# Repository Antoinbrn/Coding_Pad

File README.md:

# Taz Pad
Taz pad is a 4 key macropad, has 2 LED and works with kmk firmware.

## Firmware:
- An EC11 Rotary encoder to change volume and to mute.
- A switch to open gmail.
- A switch to open calculator.
- 2 WS2812B RGB LEDs. Both diffusing across the display.
- 4 Cherry MX-style keys.

## CAD:
The case is composed of 2 different parts. The Top and the Bottom
The case fits together with 3 M6 screws.

Top CAD

Bottom CAD

## PCB:
Here is my pcb made in KiCad

## Firmware:
This macro pad uses KMK
- the rotary encoder changes the volume, press to mute.
- Copy, Paste, Gmail, and calculator button.

## BOM:
- 4x Cherry MX Switches
- 4x DSA Keycaps
- 3x M3x16mm screws
- 5x 1N4148 DO-35 Diodes.
- 2x WS2812B LEDs
- 1x EC11 Rotary Encoder
- 1x XIAO RP2040
- 1x Case (2 printed parts)

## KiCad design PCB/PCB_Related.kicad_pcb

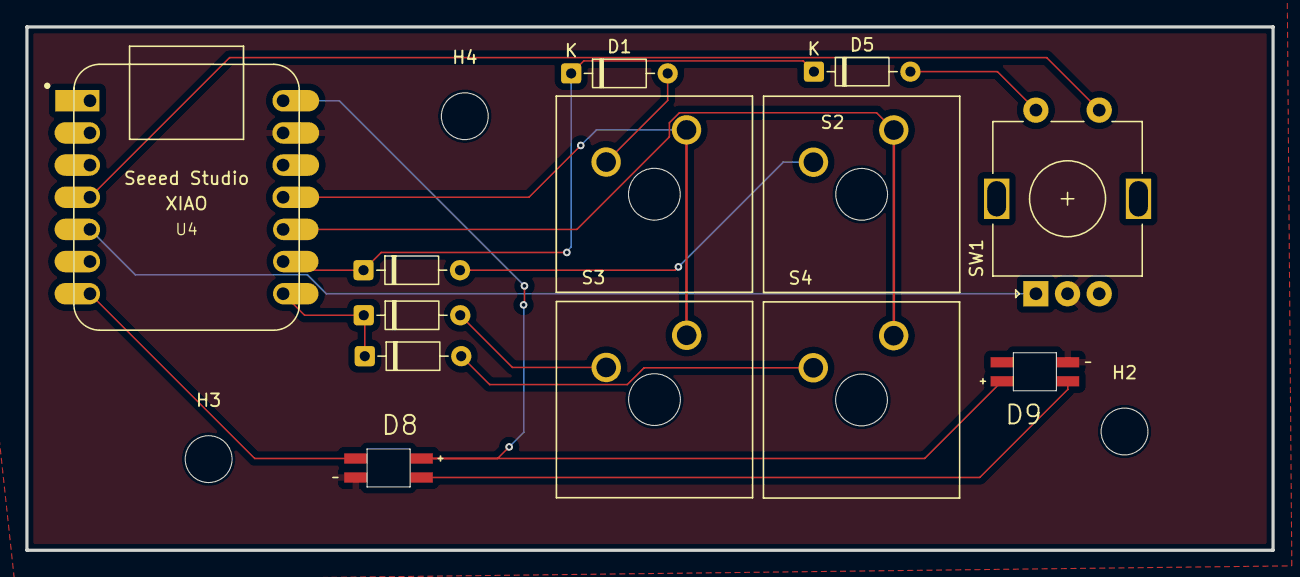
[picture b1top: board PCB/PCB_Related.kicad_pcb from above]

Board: 4 copper layers, 98.4 x 41.3 mm, 16 parts (0 on the bottom side), 16 nets.

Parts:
D1, D2, D3, D4, D5: D_Small; D_DO-35_SOD27_P7.62mm_Horizontal
D8, D9: SK6812-E; LED_SK6812-E
H2, H3, H4: MountingHole; MountingHole_3.7mm
S1, S2, S3, S4: MX1A-11NN; SW_MX1A-11NN
SW1: RotaryEncoder_Switch; RotaryEncoder_Alps_EC11E-Switch_Vertical_H20mm
U4: MOUDLE-SEEEDUINO-XIAO; XIAO-Generic-Hybrid-14P-2.54-21X17.8MM

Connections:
A: D5.2 (A), SW1.S2
AUP: SW1.A, U4.5 (PA8_A4_D4_SDA)
B: SW1.S1, U4.4 (PA11_A3_D3)
BDOWN: SW1.B, U4.6 (PA9_A5_D5_SCL)
COL0: S1.2, S3.2, U4.11 (PA6_A10_D10_MOSI)
COL1: S2.2, S4.2, U4.10 (PA5_A9_D9_MISO)
GND: D8.3 (GND), D9.3 (GND), SW1.C, U4.13 (GND)
LED: D8.4 (DIN), U4.7 (PB08_A6_D6_TX)
unnamed: D1.2 (A), S1.1
unnamed: D2.2 (A), S2.1
unnamed: D3.2 (A), S3.1
unnamed: D4.2 (A), S4.1
unnamed: D8.2 (DOUT), D9.4 (DIN)
ROW0: D1.1 (K), D2.1 (K), D5.1 (K), U4.9 (PA7_A8_D8_SCK)
ROW1: D3.1 (K), D4.1 (K), U4.8 (PB09_A7_D7_RX)
VCC: D8.1 (VDD), D9.1 (VDD), U4.14 (5V)

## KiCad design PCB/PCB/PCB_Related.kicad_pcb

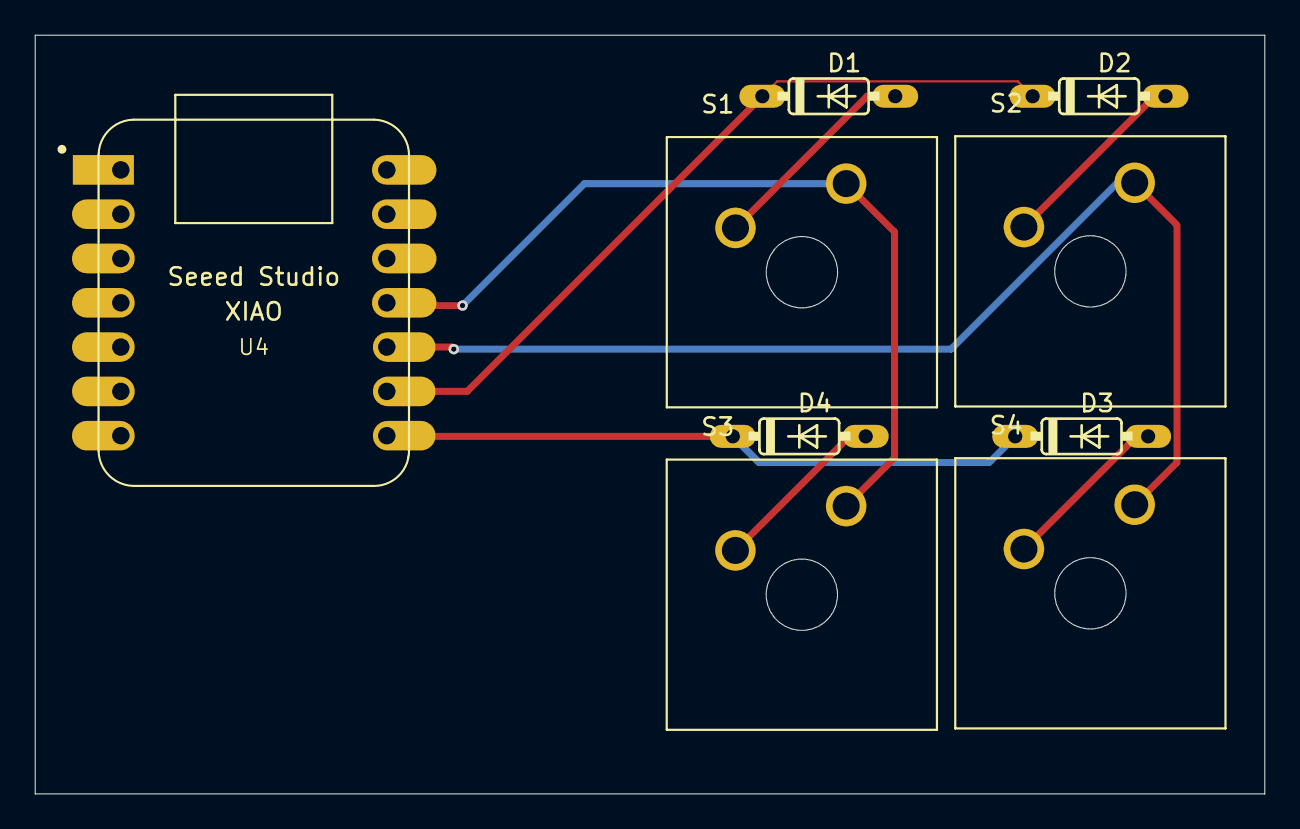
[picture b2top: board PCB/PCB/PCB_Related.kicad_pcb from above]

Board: 4 copper layers, 70.5 x 43.5 mm, 9 parts (0 on the bottom side), 8 nets.

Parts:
D1, D2, D3, D4: 1N4148; DO35-7
S1, S2, S3, S4: MX1A-11NN; SW_MX1A-11NN
U4: MOUDLE-SEEEDUINO-XIAO; XIAO-Generic-Hybrid-14P-2.54-21X17.8MM

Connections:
COL0: S1.2, S3.2, U4.11 (PA6_A10_D10_MOSI)
COL1: S2.2, S4.2, U4.10 (PA5_A9_D9_MISO)
unnamed: D1.A, S1.1
unnamed: D2.A, S2.1
unnamed: D3.A, S4.1
unnamed: D4.A, S3.1
ROW0: D1.C, D2.C, U4.9 (PA7_A8_D8_SCK)
ROW1: D3.C, D4.C, U4.8 (PB09_A7_D7_RX)

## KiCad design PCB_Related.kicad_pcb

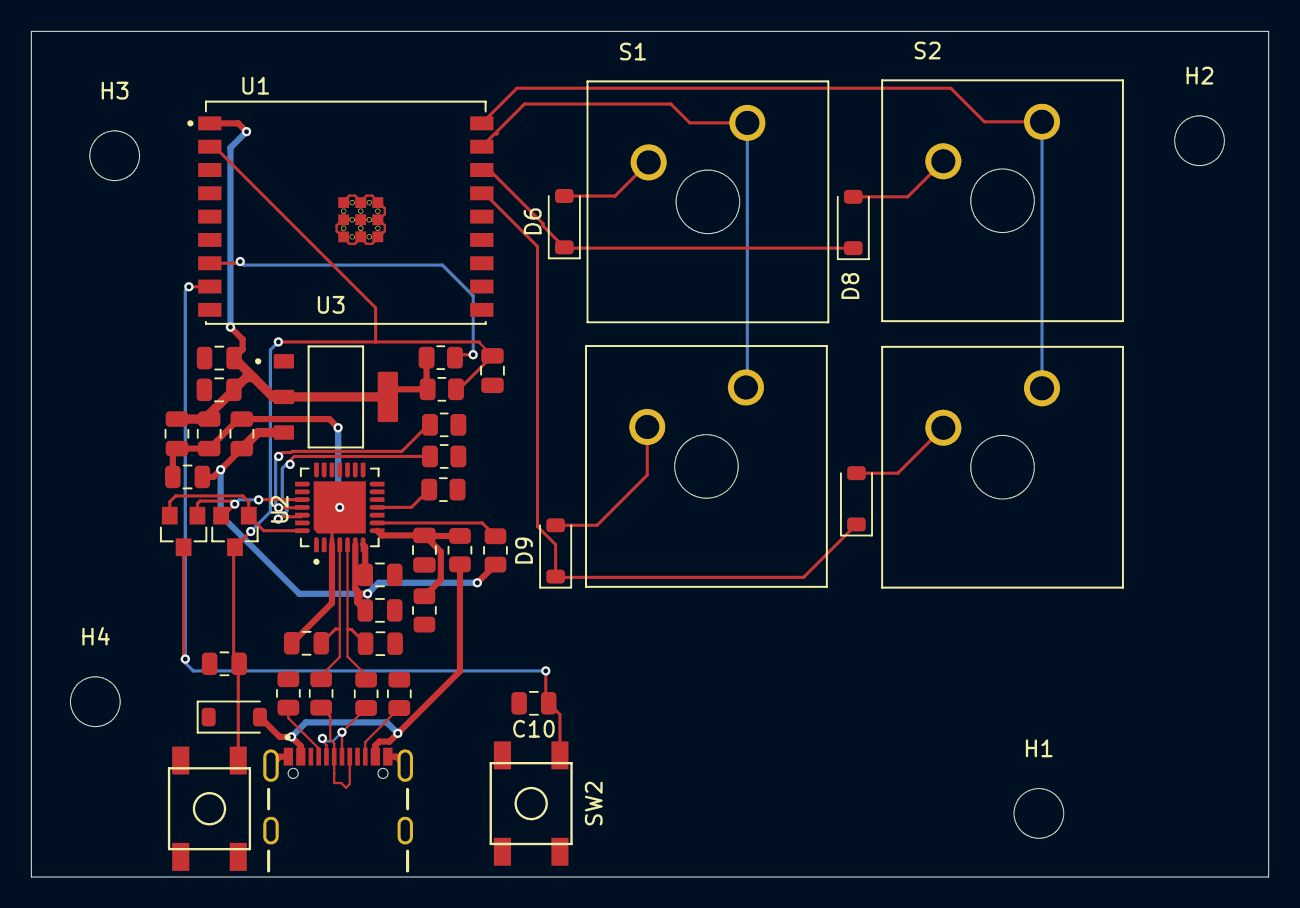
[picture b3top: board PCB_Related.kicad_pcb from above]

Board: 4 copper layers, 79.6 x 54.4 mm, 47 parts (0 on the bottom side), 29 nets.

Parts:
C1, C2: 22pF; C_0805_2012Metric
C3, C5, C7, C12, C14: 10µF/25V; C_0805_2012Metric
C4, C8: 1µF/16V; C_0805_2012Metric
C6, C9, C10, C11, C13: 0.1µF/50V; C_0805_2012Metric
D3: LESD5D5.0CT1G; D_SOD-123
D6, D8, D9, D10: Z1N5819HW-7-F; D_SOD-123
H1, H2, H3, H4: MountingHole; MountingHole_3.2mm_M3
J1: USB4105-GF-A; GCT_USB4105-GF-A
Q1, Q2: L8050QLT1G; SOT-23
R1, R2: 51k; R_0805_2012Metric
R7, R8, R13, R14: 0; R_0805_2012Metric
R9, R15, R16: 10K; R_0805_2012Metric
R10: 1K; R_0805_2012Metric
R11: 22.1K; R_0805_2012Metric
R12: 47.5K; R_0805_2012Metric
S1, S2, S3, S4: MX1A-11NN; SW_MX1A-11NN
SW1, SW2: SW_Push; SKQG-1155865
U1: ESP32-C3-WROOM-02U-N4; XCVR_ESP32-C3-WROOM-02U-N4
U2: CP2102N-A02-GQFN28R; IC_CP2102N-A02-GQFN28R
U3: AMS1117-3.3; SOT229P700X180-4N

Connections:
+3V3: C3.1, C5.2, C6.1, C7.1, C11.1, C12.1, C13.1, C14.1, R9.2, R15.1, R16.2, U1.1 (3V3), U2.6 (VDD), U2.7 (VREGIN), U3.2 (VOUT), U3.3 (VIN), U3.4
CHIP_PU: C8.1, C9.1, Q1.3, R15.2, SW1.1, U1.2 (EN)
COL0: S1.2, S3.2, U1.17 (IO1)
COL1: S2.2, S4.2, U1.18 (IO0)
DN1: J1.A7 (DN1), J1.B7 (DN2), R8.1
DP1: J1.A6 (DP1), J1.B6 (DP2), R7.1
DTR: Q1.1, Q2.2, U2.28 (DTR)
GND: C1.2, C2.2, C3.2, C4.1, C5.1, C6.2, C7.2, C8.2, C9.2, C10.2, C11.2, C12.2, C13.2, C14.2, D3.1 (K), J1.A1_B12 (GND), J1.B1_A12 (GND), J1.SH1 (SHELL_GND), J1.SH2 (SHELL_GND), J1.SH3 (SHELL_GND), J1.SH4 (SHELL_GND), R1.2, R2.2, R10.1, R12.1, SW1.2, SW2.2, U1.9 (GND), U1.19_1 (GND), U1.19_2 (GND), U1.19_3 (GND), U1.19_4 (GND), U1.19_5 (GND), U1.19_6 (GND), U1.19_7 (GND), U1.19_8 (GND), U1.19_9 (GND), U1.20_6, U1.20_7, U1.20_9, U2.3 (GND), U2.29 (EXP), U3.1 (GND/ADJ)
GPIO8: R16.1, U1.7 (IO8)
GPIO9: C10.1, Q2.3, SW2.1, U1.8 (IO9)
unnamed: D6.2 (A), S1.1
unnamed: D8.2 (A), S2.1
unnamed: D9.2 (A), S3.1
unnamed: D10.2 (A), S4.1
unnamed: J1.A5 (CC1), R2.1
unnamed: J1.B5 (CC2), R1.1
unnamed: R13.2, U2.25 (RXD)
unnamed: R14.2, U2.26 (TXD)
unnamed: C4.2, R11.1, R12.2, U2.8 (VBUS)
unnamed: R9.1, U2.9 (~RST)
unnamed: R10.2, U2.11 (~SUSPEND)
ROW0: D6.1 (K), D8.1 (K), U1.16 (IO2)
ROW1: D9.1 (K), D10.1 (K), U1.15 (IO3)
RTS: Q1.2, Q2.1, U2.24 (RTS)
U0RXD: R14.1, U1.11 (RXD/IO20)
U0TXD: R13.1, U1.12 (TXD/IO21)
USB_DN: C1.1, R8.2, U2.5 (D-)
USB_DP: C2.1, R7.2, U2.4 (D+)
VBUS: D3.2 (A), J1.A4_B9 (VBUS), J1.B4_A9 (VBUS), R11.2
